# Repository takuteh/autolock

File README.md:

# オートロック

## GPIO など

リセットボタン（未実装）GPIO 27  
リードスイッチ GPIO 3  
開錠ボタン GPIO 9  
施錠ボタン GPIO 2  
サーボモーター（上側）GPIO 19  
サーボモーター（下側）GPIO 6  
モーター電源用リレー　 GPIO 22

## 運用方法・注意事項

<ins>**1.direct_version(鍵・モーター直結型)**</ins>

- 鍵に直接モーターを取り付けて制御する方式である
  ソースは direct_version 以下

- lock.sh を crontab に記述すれば、起動時に実行されるようになる

- main.py を実行すればオートロックが起動するが、sudo で実行する必要がある

- main.py は C 言語で記述された関数を呼び出しているので、C ディレクトリ内のプログラムを使用する

- ferica 登録は　 read_idm.py 　を実行する、その際他のプログラムなどで
  カードーリーダーを使用していると読み取りができないため全て停止させてから
  読み取りを行う

- 読み取られた idm は idm_list.txt に登録され、プログラムもそのリストから読み出す

- idm_list.txt の一行目がなぜか読み取られないので二行目以降に記述

<ins>**2.gear_version(ギアボックス付きの制御機構)**</ins>

- 施錠・解錠を手動でも行えるようにギアボックス付きのオートロックを追加した
  ソースは `gear_version` 以下

- **セットアップ**
  下記コマンドを実行すれば以下の処理や設定が全て行われる

  ```
  cd gear_version
  mkdir build
  cd build
  cmake ..
  make
  cd ..
  sudo setup.sh
  ```

- **依存関係**  
  `pigpio`,`mosquitto`,`libmosquitto-dev`,`libcurl4-openssl-dev`  
  json は[nlohmann/json](https://github.com/nlohmann/json)ライブラリを使用  
  curl は LINE,Slack の API で使用するため、API を使用しない場合は不要

- **実行ファイル**  
  バイナリは`gear_version/bin`に生成される  
  systemd に autolock のプログラムを登録することで自動起動させることができる  
  Unit ファイルは`gear_version/service/autolock.service`である  
  実行プログラムのパスをバイナリのあるディレクトリに修正する必要あり

- **設定関係**  
  `gear_version/etc/autolock_setting.json`で各種設定を行う  
  以下の各項目について設定が可能である

  - メインの動作設定はオートロックの有無効,ドアの開放時の閉ボタンの動作,鍵の回転方向
    未施錠の場合のタイムアウト秒数,施錠までの秒数を設定する,"no"とすれば無制限
  - MQTT は開錠・施錠・リレー制御のトピック、メッセージ、mqtt ポート、ブローカー ip
  - LINE はチャンネルのアクセストークン、送信先ユーザー ID
  - Slack はチャンネルのアクセストークン、送信先のチャンネル名
  - `/etc/mosquitto/mosquitto.conf`を変更し、mqtt のポート設定と外部からのアクセス許可をする必要あり

- **ライブラリ**  
  外部ライブラリとして`nlohmann/json`,`pigpiod_if2`,`mosquitto`  
  独自ライブラリとして`control_servo`,`min_mqtt`,`autolock_setting`,`line_api`,`slack_api`がある、これらはビルドすると`gear_version/lib`内に配置される  
  `line_api`,`slack_api`は LINE と Slack に通知をするライブラリである

- **テストコード**  
  各種テストコードのビルド先はビルドディレクトリの`src/test_code`内  
  `line_test`と`slack_test`はアクセストークンと送信先をソース内を変更して設定する必要がある  
  `gear_version/src/test_code`内にすべてのソースコードがある  
  作者の環境ではラズパイとモーターの電源は別で取っているので、モーターの動作が不安定になった場合に備えリレーで電源を制御している  
  `reray_on`,`reray_off` でそれぞれ電源の入切が可能である

- サーボモーター MG996R の使用を前提としたギアボックスの 3DCAD データ(stl 形式)は 3D_Models 以下にある

- Eagle で作成した基板データは pcb_data 以下にある([説明](https://github.com/takuteh/autolock/blob/main/pcb_data/READMD.md))

- **API**  
  オートロックの内部 API として MQTT を利用している.
  以下の例のように json 形式でブローカーに目的の動作のトピック名を指定し,メッセージ送信を行う．
  
  **フルメッセージ**
  ```
  {"app":"LINE","message":"1","user":"takuteh"}
  ```

  app,user 要素は，それぞれ通知を行う際にどのアプリから制御を行なったか，誰が操作をしたのかを判別することが可能．
  上記の例で`/door/open`トピックに送信すると`「takutehがLINEで開錠しました」`という通知が行われる.message 要素は必須だが，それ以外は指定しなくても動作する.
  
  **最小構成のメッセージ**
  ```
  {"message":"1"}
  ```

  「unknown が MQTT で開錠しました」という通知が行われる.

  **mosquitto での送信例(broker ip 192.168.1.1 の場合)**
  ```
  mosquitto_pub -h 192.168.1.1 -t "/door/open" -m '{"app":"LINE","message":"1","user":"takuteh"}'
  ```

## ディレクトリ構成

※一部省略

<pre>
autolock/
├── 3D_Models
│   └── ...
├── pcb_data
│   └── ...
├── README.md
├── direct_version
│   ├── C
│   │   ├── Makefile
│   │   ├── close.c
│   │   └── open.c
│   ├── C++
│   │   ├── src
│   │   │   ├── auto_lock.cpp
│   │   │   ├── auto_lock.hpp
│   │   │   ├── switch.cpp
│   │   │   └── switch.hpp
│   │   ├── test
│   │   └── test.cpp
│   ├── Python
│   │   ├── direct_lock.service
│   │   ├── main.py
│   │   └── read_idm.py
│   └── README.txt
└── gear_version
    ├── CMakeLists.txt             :全体のビルド用
    ├── etc
    │   └── autolock_setting.json :設定ファイル
    ├── include                 
    │   ├── autolock_setting.h
    │   ├── control_servo.h
    │   ├── line_api.h
    │   ├── min_mqtt.h
    │   └── slack_api.h
    ├── service
    │   └── autolock.service    :systemdのserviceファイル
    ├── setup.sh                 :初回ビルド前に実行するスクリプト
    └── src
        ├── autolock.cpp         :メインのコード
        ├── autolock_setting.cpp :設定ファイルの読込
        ├── control_servo.cpp    :サーボモーター制御
        ├── line_api.cpp         :LINEへ送信する
        ├── min_mqtt.cpp         :MQTT関連の制御・設定
        ├── slack_api.cpp        :Slackへ送信
        ├── test_code            :デバッグ用コード
        │   ├── CMakeLists.txt  :test_codeのビルド用
        │   ├── down_close.c
        │   ├── down_open.c
        │   ├── line_test.cpp
        │   ├── read_sw.cpp
        │   ├── relay_off.cpp
        │   ├── relay_on.cpp
        │   ├── slack_test.cpp
        │   ├── up_close.c
        │   └── up_open.c
        └── wiringPi_ver
            ├── home_close.c
            ├── home_open.c
            └── lock_open.c
</pre>

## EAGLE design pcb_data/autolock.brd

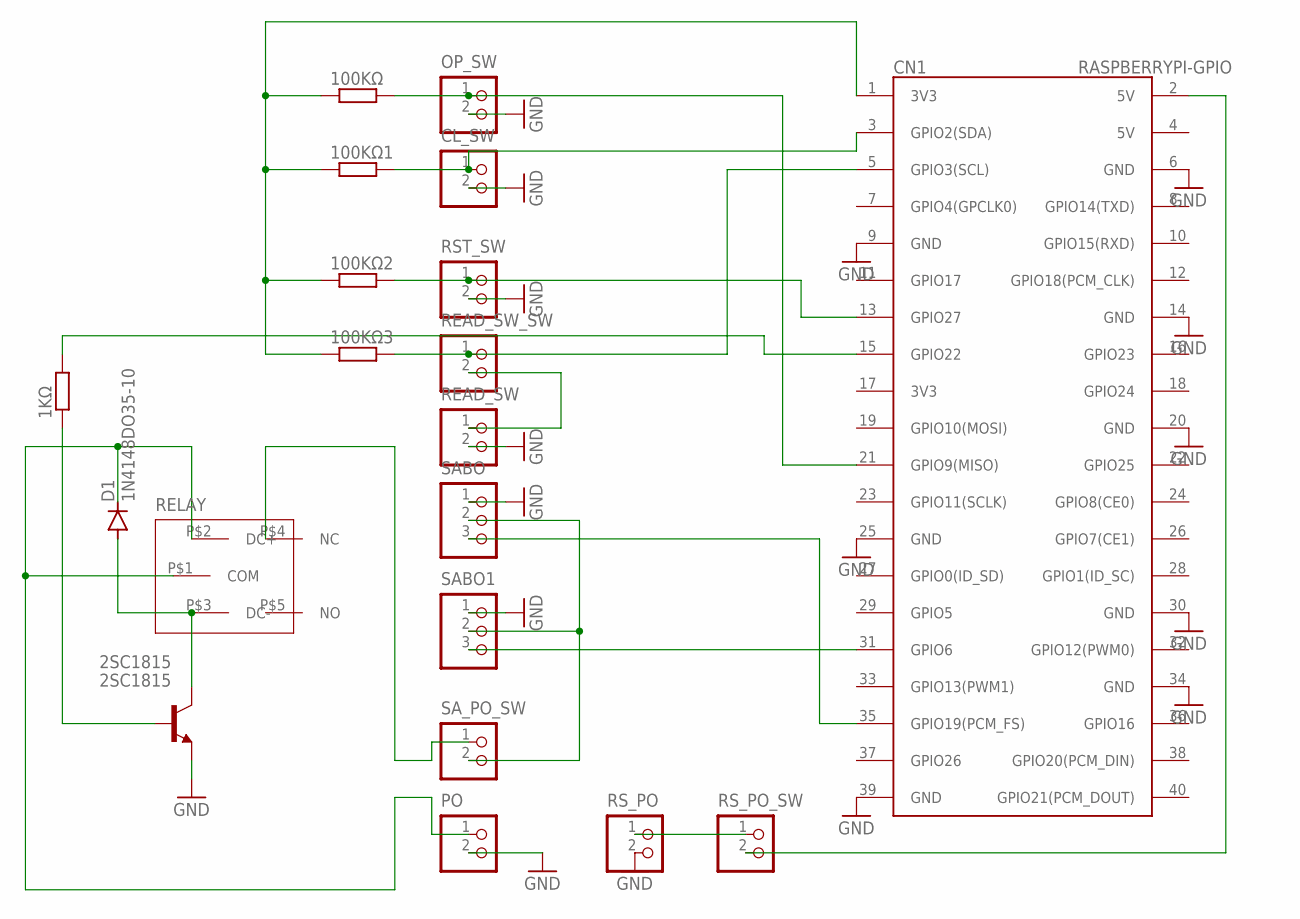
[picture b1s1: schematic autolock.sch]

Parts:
1KΩ, 100KΩ, 100KΩ1, 100KΩ2, 100KΩ3: R-EU_0207/10; 0207/10
2SC1815: 2SC1815; TO92-ECB
CL_SW: B2B-XH-A
CN1: RASPBERRYPI-GPIO; 2X20-BOLD
D1: 1N4148DO35-10; DO35-10
OP_SW: B2B-XH-A
PO: B2B-XH-A
READ_SW: B2B-XH-A
READ_SW_SW: B2B-XH-A
RELAY: SRD05VDCSLC
RST_SW: B2B-XH-A
RS_PO: B2B-XH-A
RS_PO_SW: B2B-XH-A
SABO, SABO1: B3B-XH-A
SA_PO_SW: B2B-XH-A

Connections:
GND: 2SC1815.E, CL_SW.2, CN1.6 (GND), CN1.9 (GND), CN1.14 (GND), CN1.20 (GND), CN1.25 (GND), CN1.30 (GND), CN1.34 (GND), CN1.39 (GND), OP_SW.2, PO.2, READ_SW.2, RST_SW.2, RS_PO.2, SABO.1, SABO1.1
unnamed: 2SC1815.C, D1.A, RELAY.P$3 (DC-)
unnamed: RS_PO.1, RS_PO_SW.1
unnamed: 100KΩ.1, 100KΩ1.1, 100KΩ2.1, 100KΩ3.1, CN1.1 (3V3)
unnamed: 1KΩ.2, CN1.15 (GPIO22)
unnamed: 100KΩ1.2, CL_SW.1, CN1.3 (GPIO2(SDA))
unnamed: SABO.2, SABO1.2, SA_PO_SW.2
unnamed: CN1.35 (GPIO19(PCM_FS)), SABO.3
unnamed: D1.C, PO.1, RELAY.P$1 (COM), RELAY.P$2 (DC+)
unnamed: CN1.31 (GPIO6), SABO1.3
unnamed: READ_SW.1, READ_SW_SW.2
unnamed: RELAY.P$4 (NC), SA_PO_SW.1
unnamed: CN1.2 (5V), RS_PO_SW.2
unnamed: 1KΩ.1, 2SC1815.B
unnamed: 100KΩ.2, CN1.21 (GPIO9(MISO)), OP_SW.1
unnamed: 100KΩ3.2, CN1.5 (GPIO3(SCL)), READ_SW_SW.1
unnamed: 100KΩ2.2, CN1.13 (GPIO27), RST_SW.1

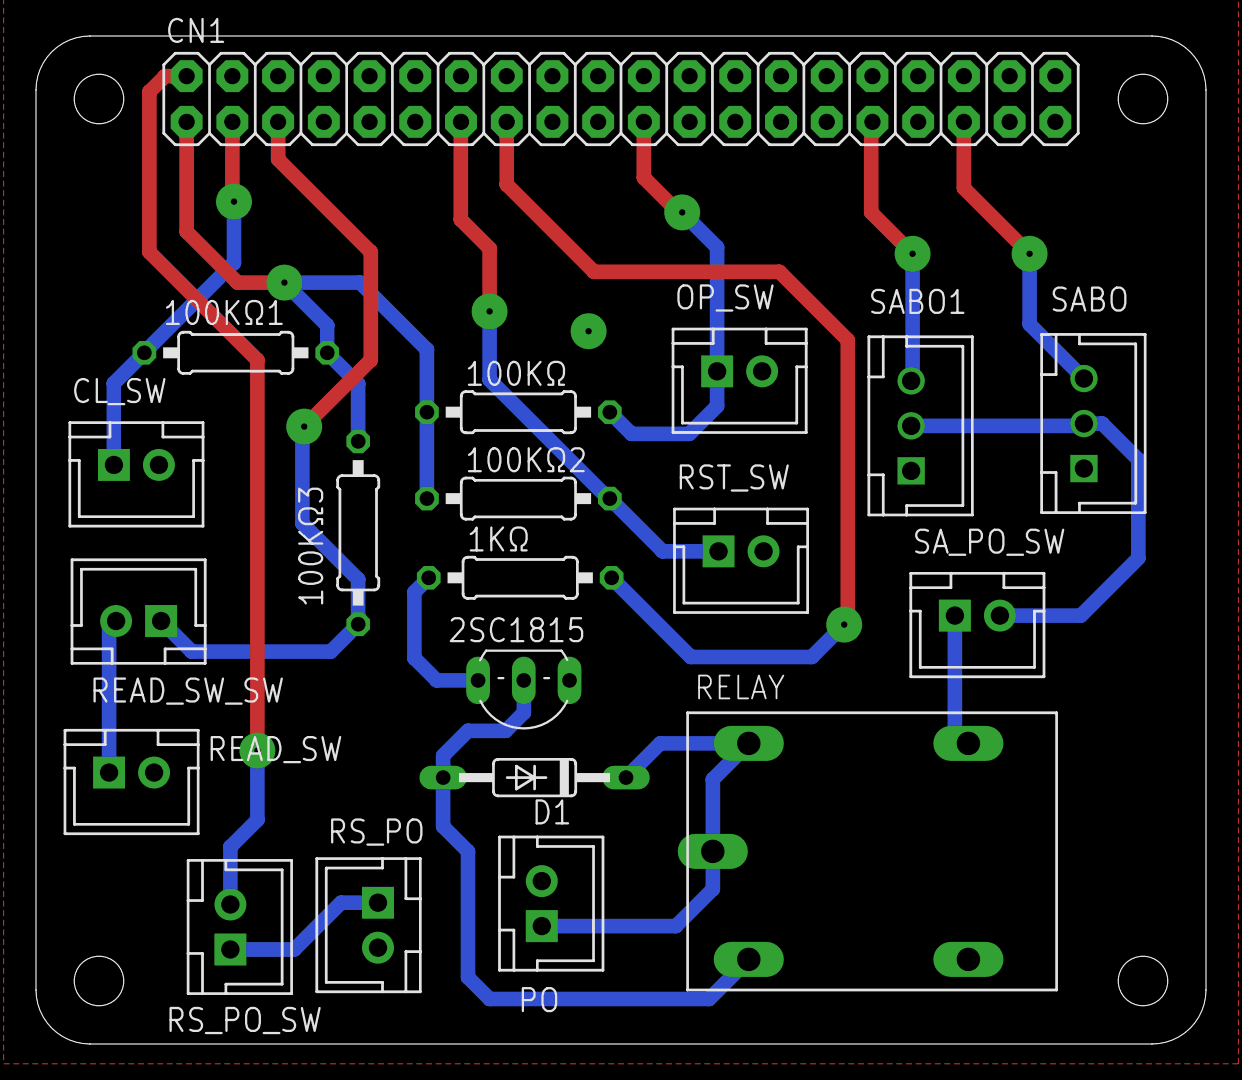
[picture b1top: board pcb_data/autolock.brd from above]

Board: 2 copper layers, 65.0 x 56.0 mm, 20 parts (0 on the bottom side), 17 nets.

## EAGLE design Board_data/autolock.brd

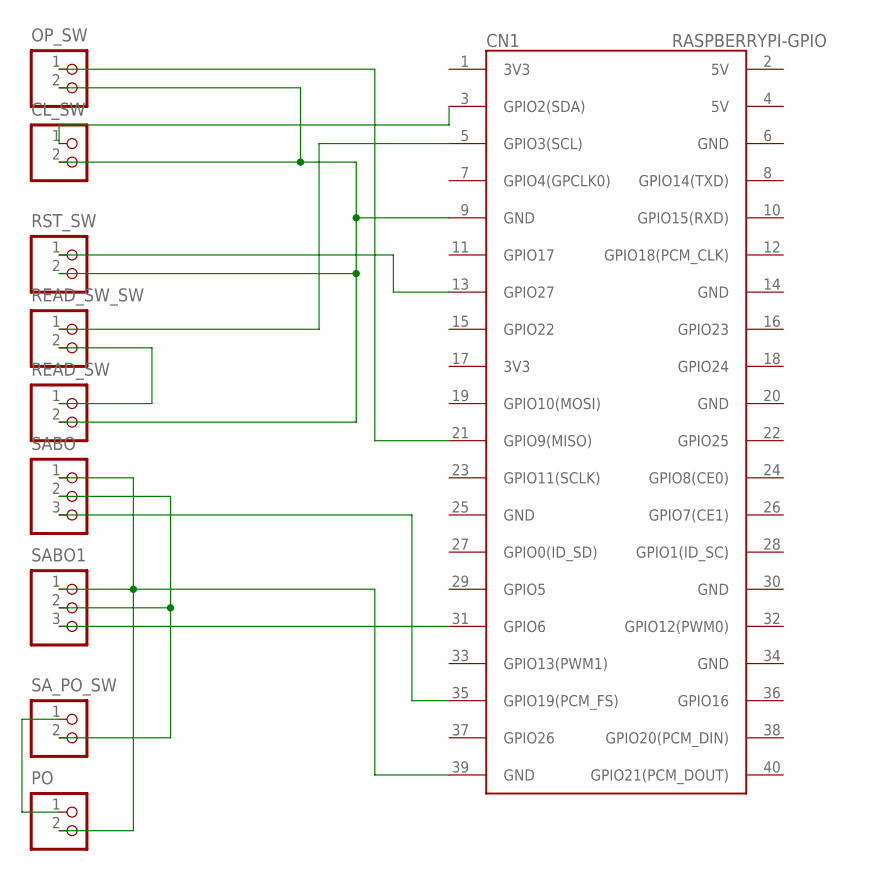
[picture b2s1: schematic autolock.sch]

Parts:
CL_SW: B2B-XH-A
CN1: RASPBERRYPI-GPIO; 2X20-BOLD
OP_SW: B2B-XH-A
PO: B2B-XH-A
READ_SW: B2B-XH-A
READ_SW_SW: B2B-XH-A
RST_SW: B2B-XH-A
SABO, SABO1: B3B-XH-A
SA_PO_SW: B2B-XH-A

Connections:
GND: CL_SW.2, CN1.9 (GND), CN1.39 (GND), OP_SW.2, PO.2, READ_SW.2, RST_SW.2, SABO.1, SABO1.1
unnamed: CN1.21 (GPIO9(MISO)), OP_SW.1
unnamed: CL_SW.1, CN1.3 (GPIO2(SDA))
unnamed: CN1.5 (GPIO3(SCL)), READ_SW_SW.1
unnamed: PO.1, SA_PO_SW.1
unnamed: SABO.2, SABO1.2, SA_PO_SW.2
unnamed: CN1.35 (GPIO19(PCM_FS)), SABO.3
unnamed: CN1.31 (GPIO6), SABO1.3
unnamed: READ_SW.1, READ_SW_SW.2
unnamed: CN1.13 (GPIO27), RST_SW.1

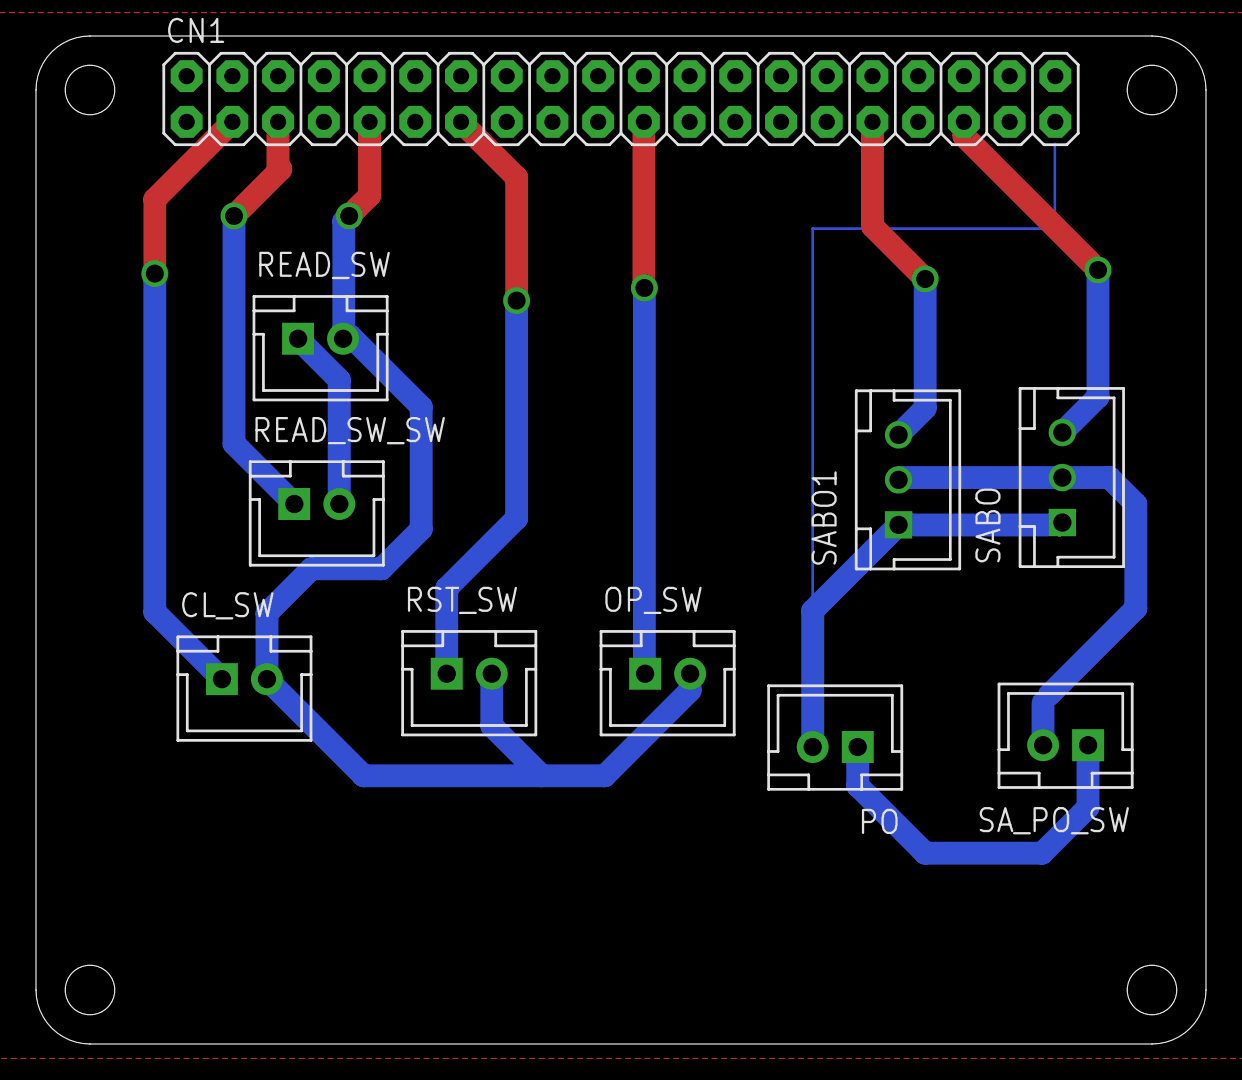
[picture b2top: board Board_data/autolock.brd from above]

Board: 2 copper layers, 65.0 x 56.0 mm, 10 parts (0 on the bottom side), 10 nets.

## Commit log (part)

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2023-08-13 pythonでは一通り機能が完成している
2023-12-27 ギアボックス機構追加
2024-01-31 サーボモーターコード修正
2024-02-09 基板・ケースデータ追加
2024-02-10 pigpioでサーボモーター制御を書き直した
2024-02-11 割り込み完成・ディレクトリ整理
2024-02-19 基板修正・リードスイッチ調整
2024-02-25 mqtt実装・基板修正
2024-04-02 リレーの制御を追加
2024-06-04 Makefile追加・README修正
2024-06-04 3Dmodel・README修正
2024-06-08 setup.sh追加、unitファイル修正
2024-06-11 不要なファイルを削除
2024-07-27 CMake追加、ファイル読込部分修正
2024-07-30 test_code関連cmake化
2024-08-06 direct_version、C修正
2024-08-17 LINEに通知＆設定読み込み変更
2024-08-18 リードスイッチ周り修正
2024-08-21 api部分修正＆slack api追加
2024-08-21 設定項目追加・mainスレッド処理修正
2024-08-25 main施錠通知追加・APIテストコード追加
2024-08-25 README修正
2024-08-28 施錠フラグ追加、タイムアウト処理改良
2024-08-28 mqttメッセージjson化
2024-08-28 不要なMakefile削除
2024-08-28 READMEディレクトリ構成追記
2024-10-07 基板データ修正
2024-10-07 serviceファイル修正,after->mosquitto
2024-10-08 基板GND周り修正、実装図追加
2024-10-12 PCB用README作成
2024-11-23 リードセンサー周りコメントアウト
2024-11-23 test_code,relay_offをCMakeに追加
2024-12-13 setup.sh mqtt追記されてしまう問題修正
2024-12-13 setup.sh aptオプションy,cmake追加
2025-03-30 施錠までのタイムアウトを設定ファイルから設定するように変更
2025-04-20 pthreadライブラリのリンクを追加
2025-04-20 回転方向を設定項目に追加
2025-04-21 オートロックの有効・無効を設定に追加
2025-04-21 ドアが空いている際にclose swを無視するかを設定項目に追加
2025-04-29 setting.jsonコメント削除
2025-04-29 3Dmodel修正
2025-07-04 setting.jsonの形式変更，mqtt受信処理をループに変更
2025-07-12 dbの認証を通すように変更
2025-07-12 認証を行うかどうかの設定を追加
2025-07-12 オートロックの有効化，リードセンサーの無視の設定をbool型に変更
2025-07-13 ユーザー認証に時刻の比較を追加
2025-07-13 設定変更用のトピックを追加
2025-07-13 設定再読み込み用の処理を追加
2025-07-13 mqttで設定変更をできるように変更
2025-07-13 モーターリセットをオンとオフに分割
2025-07-13 不要な部分を削除
2025-07-15 認証周りのバグ修正
2025-07-15 不要なトピックの処理を削除
2025-07-16 起動時に設定内容をmqttで送信できるようにした
2025-07-19 appで操作したときのみ別のチャンネルにも送信できるようにした
2025-07-19 認証する際app名を小文字に直すように修正
2025-08-17 権限のないユーザーの操作通知にline idを入れるように変更
